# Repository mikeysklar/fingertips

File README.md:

fingertips
---

4 button I2C keypad used in combination with:

* [5wayjoy](https://github.com/mikeysklar/5wayjoy) - 5 way tactile joystick I2C STEMMA
* [QtHub](https://github.com/mikeysklar/qthub) - 4 way multidirectional hub I2C STEMMA
* [old-softie](https://github.com/mikeysklar/old-softie) -  3 soft silicon buttons I2C STEMMA

An addition I2C hub and controller is used to run the CircuitPython code needed to translate chords into ascii chars.

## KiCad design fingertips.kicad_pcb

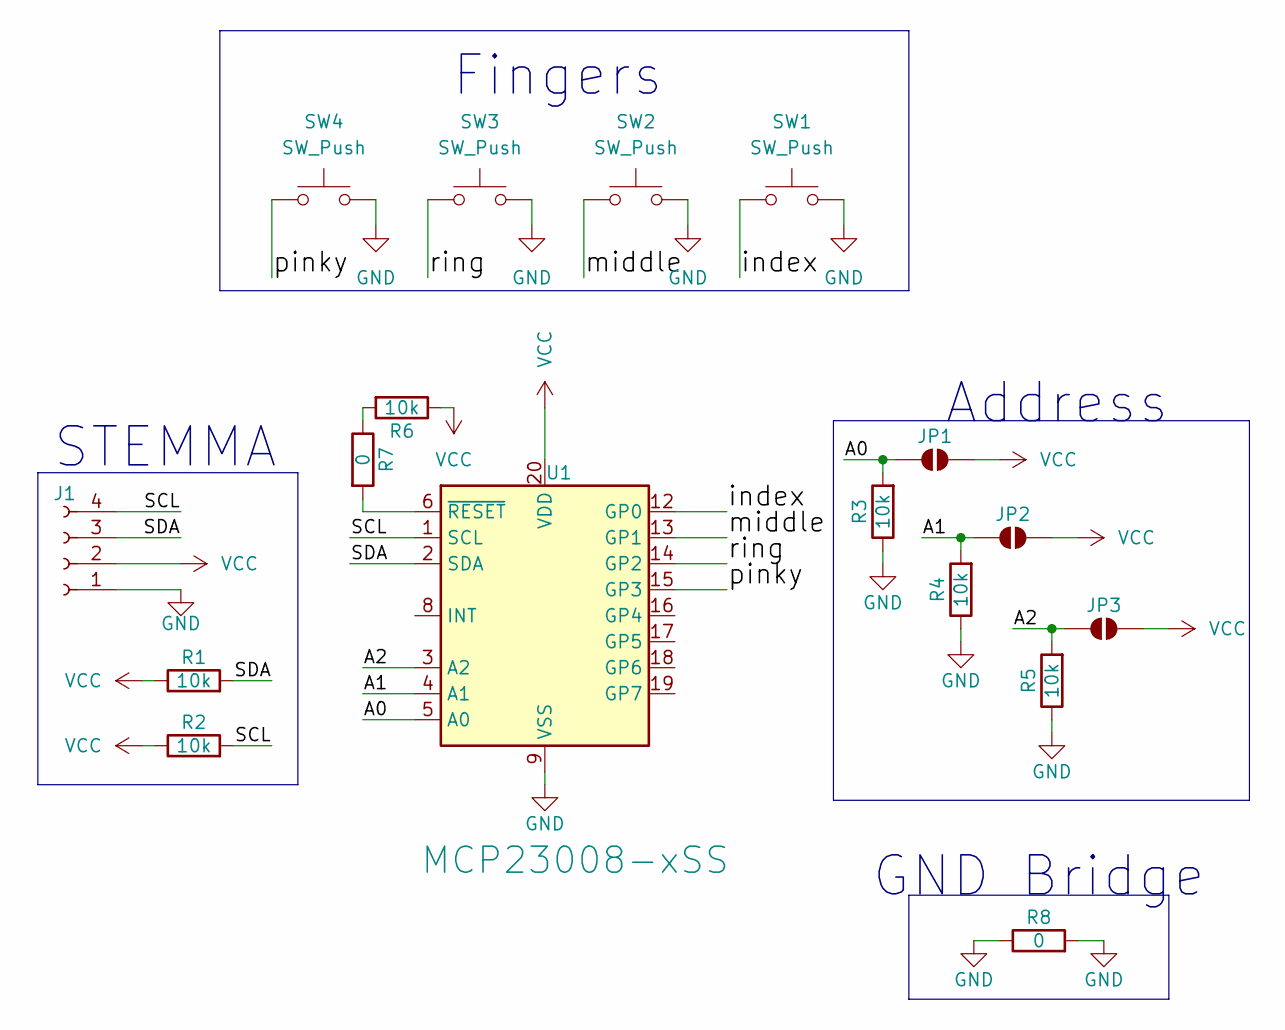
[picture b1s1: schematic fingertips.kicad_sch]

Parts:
J1: Conn_01x04_Socket; JST_SH4
JP1, JP2, JP3: SolderJumper_2_Open; SolderJumper-2_P1.3mm_Open_TrianglePad1.0x1.5mm
R1, R2, R3, R4, R5, R6: 10k; R_0805_2012Metric_Pad1.20x1.40mm_HandSolder
R7, R8: 0; R_0805_2012Metric_Pad1.20x1.40mm_HandSolder
SW1, SW2, SW3, SW4: SW_Push; SW_SPST_PTS645
U1: MCP23008-xSS; SSOP-20_5.3x7.2mm_P0.65mm

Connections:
/A0: JP1.1 (A), R3.2, U1.5 (A0)
/A1: JP2.1 (A), R4.2, U1.4 (A1)
/A2: JP3.1 (A), R5.2, U1.3 (A2)
/SCL: J1.4, R2.2, U1.1 (SCL)
/SDA: J1.3, R1.2, U1.2 (SDA)
/index: SW1.1, U1.12 (GP0)
/middle: SW2.1, U1.13 (GP1)
/pinky: SW4.1, U1.15 (GP3)
/ring: SW3.1, U1.14 (GP2)
GND: J1.1, R3.1, R4.1, R5.1, R8.1, R8.2, SW1.2, SW2.2, SW3.2, SW4.2, U1.9 (VSS)
unnamed: R6.2, R7.1
unnamed: R7.2, U1.6 (~RESET)
VCC: J1.2, JP1.2 (B), JP2.2 (B), JP3.2 (B), R1.1, R2.1, R6.1, U1.20 (VDD)

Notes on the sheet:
Address
GND Bridge
Fingers
STEMMA

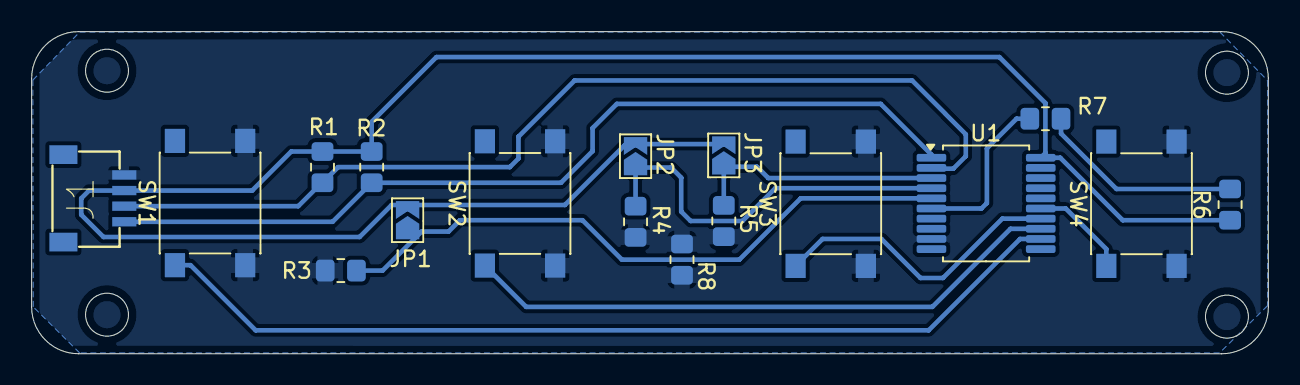
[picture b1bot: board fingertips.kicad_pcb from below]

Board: 2 copper layers, 79.2 x 20.6 mm, 17 parts (17 on the bottom side), 13 nets.

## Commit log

2025-03-03 readme pics
2025-03-03 kicad
2025-03-16 who dis
